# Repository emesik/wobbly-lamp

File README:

wobbly lamp

Lamp which reacts to movement by changing colors.

It associates red, green and blue components with X, Y and Z axes respectively. The deflection from
initial position is linearly converted to light volume in each axis and returns to normal with
decay adjustable by a potentiometer unless the lamp gets bumped again.

Hardware required:
	* 12V supply,
	* MMA7361 accelerometer breakout board,
	* RGB LED strip or other similar light source with common anode,
	* 50x50mm single layer board to make the PCB,
	* electronic components as listed in the KiCad project (ATmega8, 3×N-FET, 3V3 regulator and
	  a bunch of resistors, capacitors and connectors),

This project aims to be an example of ATmega MCU's use of:
	* PWM (pulse width modulation),
	* ADC (analog to digital conversion),
	* interrupts (timer and ADC),

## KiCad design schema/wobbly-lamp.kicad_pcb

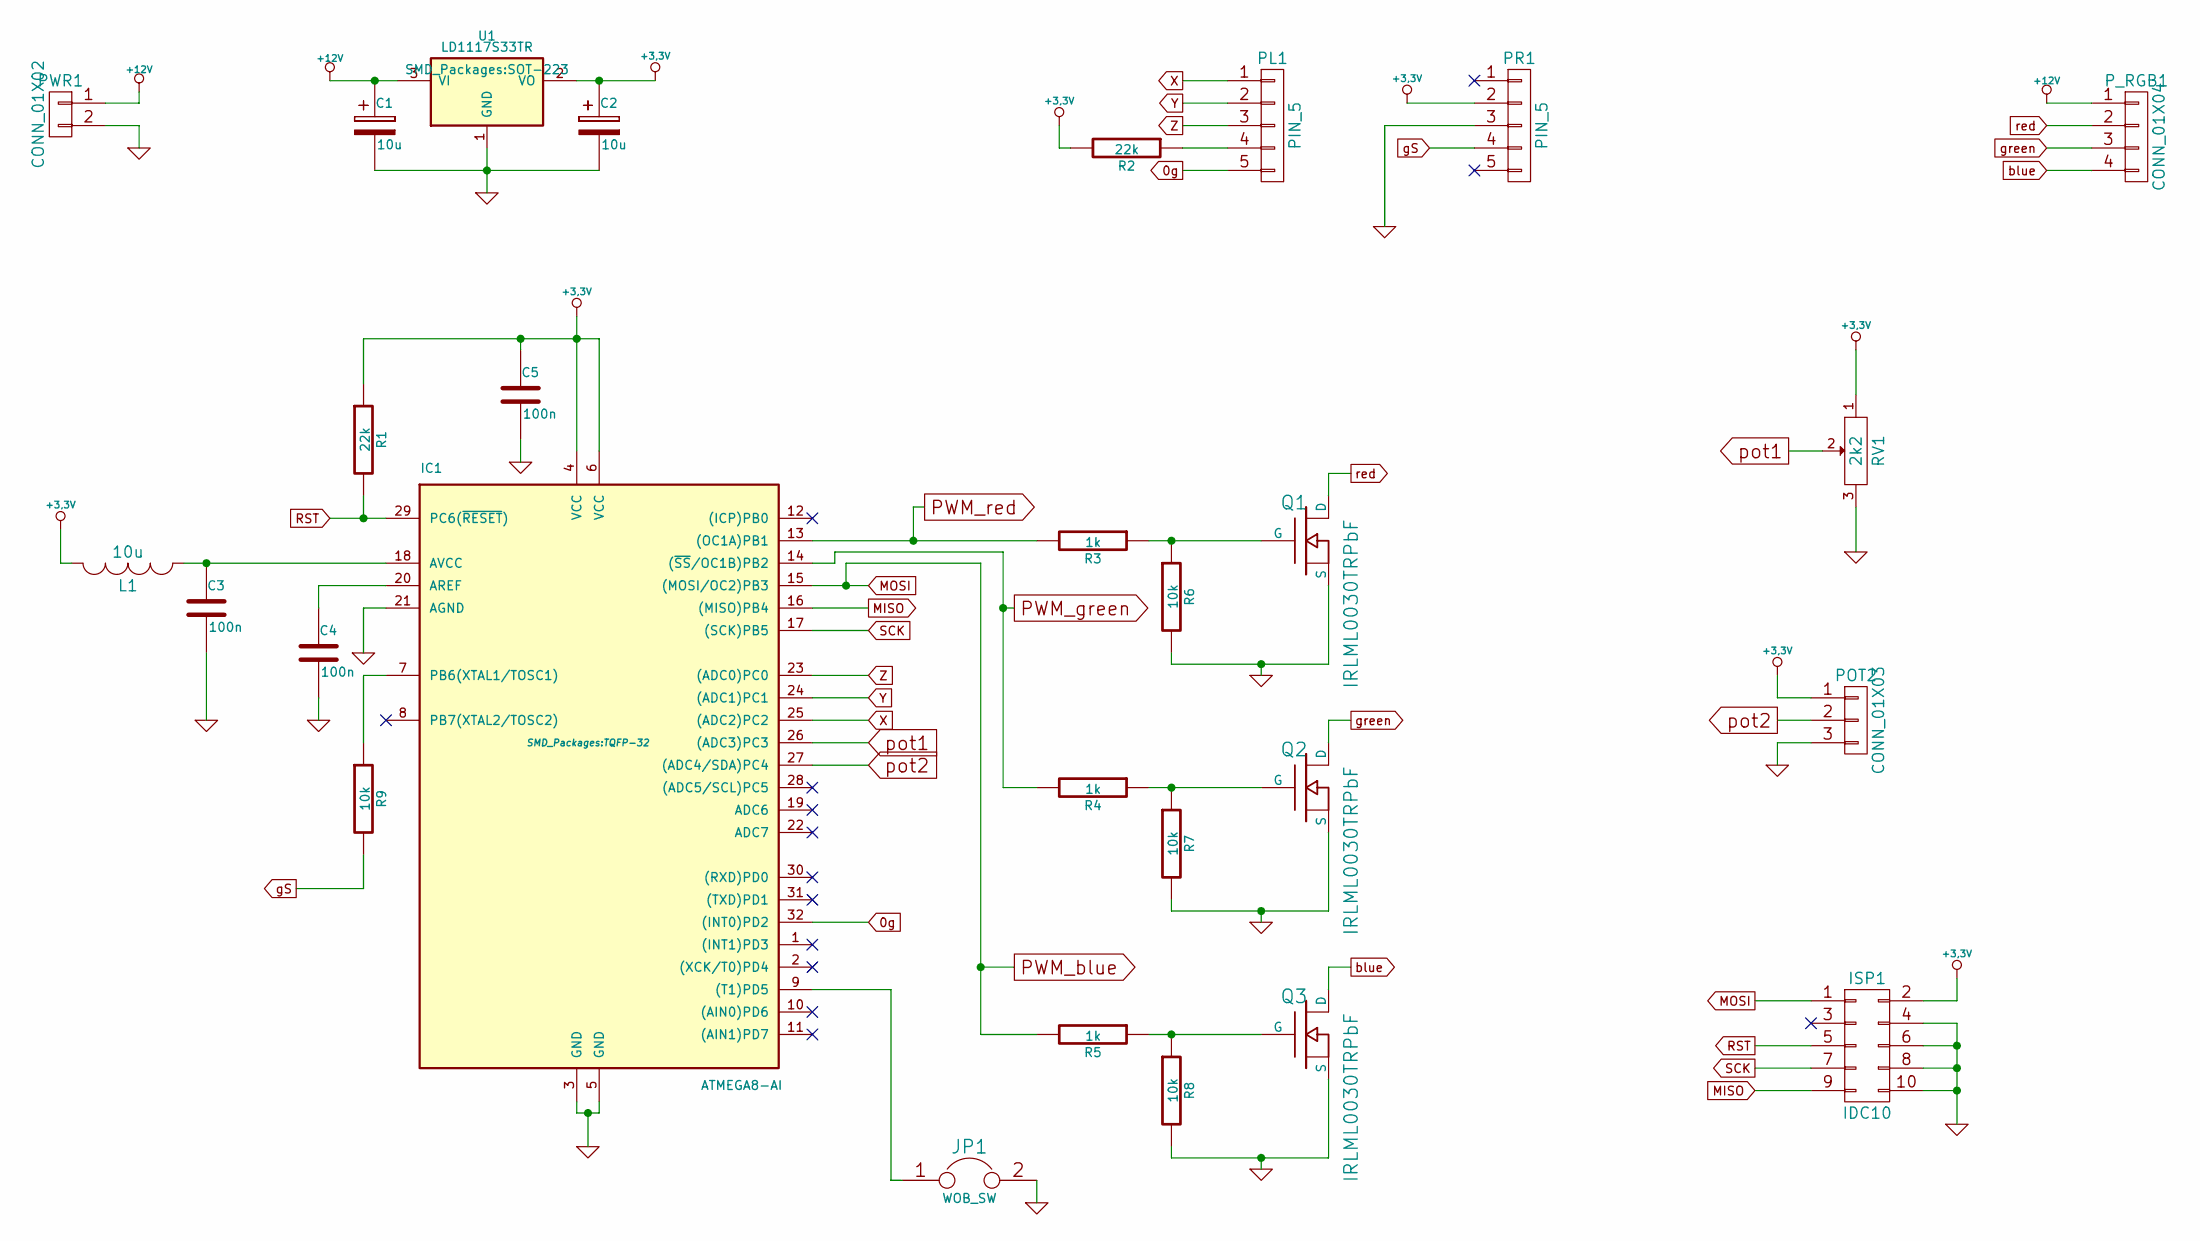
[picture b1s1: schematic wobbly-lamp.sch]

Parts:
C1, C2: 10u; Capacitor5x6RM2.5
C3, C4, C5: 100n; C_0805_HandSoldering
IC1: ATMEGA8-AI; TQFP-32
ISP1: IDC10; Pin_Header_Straight_2x05
JP1: WOB_SW; Pin_Header_Straight_1x02
L1: 10u; SMD-0805
PL1: PIN_5; Pin_Header_Straight_1x05
POT2: CONN_01X03; Pin_Header_Straight_1x03
PR1: PIN_5; Pin_Header_Straight_1x05
PWR1: CONN_01X02; AK300-2
P_RGB1: CONN_01X04; AK300-4
Q1, Q2, Q3: IRLML0030TRPbF; SOT23_FET_Handsoldering
R1, R2: 22k; R_0805_HandSoldering
R3, R4, R5: 1k; R_0805_HandSoldering
R6, R7, R8, R9: 10k; R_0805_HandSoldering
RV1: 2k2; Potentiometer_VishaySpectrol-Econtrim-Type36T
U1: LD1117S33TR; SOT-223

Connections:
0g: IC1.32 ((INT0)PD2), PL1.5
+3.3V: C2.1, C5.1, IC1.4 (VCC), IC1.6 (VCC), ISP1.2, L1.2, POT2.1, PR1.2, R1.1, R2.2, RV1.1, U1.2 (VO)
+12V: C1.1, PWR1.1, P_RGB1.1, U1.3 (VI)
GND: C1.2, C2.2, C3.2, C4.2, C5.2, IC1.3 (GND), IC1.5 (GND), IC1.21 (AGND), ISP1.4, ISP1.6, ISP1.8, ISP1.10, JP1.2, POT2.3, PR1.3, PWR1.2, Q1.S, Q2.S, Q3.S, R6.2, R7.2, R8.2, RV1.3, U1.1 (GND)
MISO: IC1.16 ((MISO)PB4), ISP1.9
unnamed: C3.1, IC1.18 (AVCC), L1.1
unnamed: C4.1, IC1.20 (AREF)
unnamed: IC1.7 (PB6(XTAL1/TOSC1)), R9.1
unnamed: IC1.9 ((T1)PD5), JP1.1
unnamed: PL1.4, R2.1
unnamed: Q1.G, R3.1, R6.1
unnamed: Q2.G, R4.1, R7.1
unnamed: Q3.G, R5.1, R8.1
PWM_blue: IC1.15 ((MOSI/OC2)PB3), ISP1.1, R5.2
PWM_green: IC1.14 ((~SS~/OC1B)PB2), R4.2
PWM_red: IC1.13 ((OC1A)PB1), R3.2
RST: IC1.29 (PC6(~RESET~)), ISP1.5, R1.2
SCK: IC1.17 ((SCK)PB5), ISP1.7
X: IC1.25 ((ADC2)PC2), PL1.1
Y: IC1.24 ((ADC1)PC1), PL1.2
Z: IC1.23 ((ADC0)PC0), PL1.3
blue: P_RGB1.4, Q3.D
gS: PR1.4, R9.2
green: P_RGB1.3, Q2.D
pot1: IC1.26 ((ADC3)PC3), RV1.2
pot2: IC1.27 ((ADC4/SDA)PC4), POT2.2
red: P_RGB1.2, Q1.D

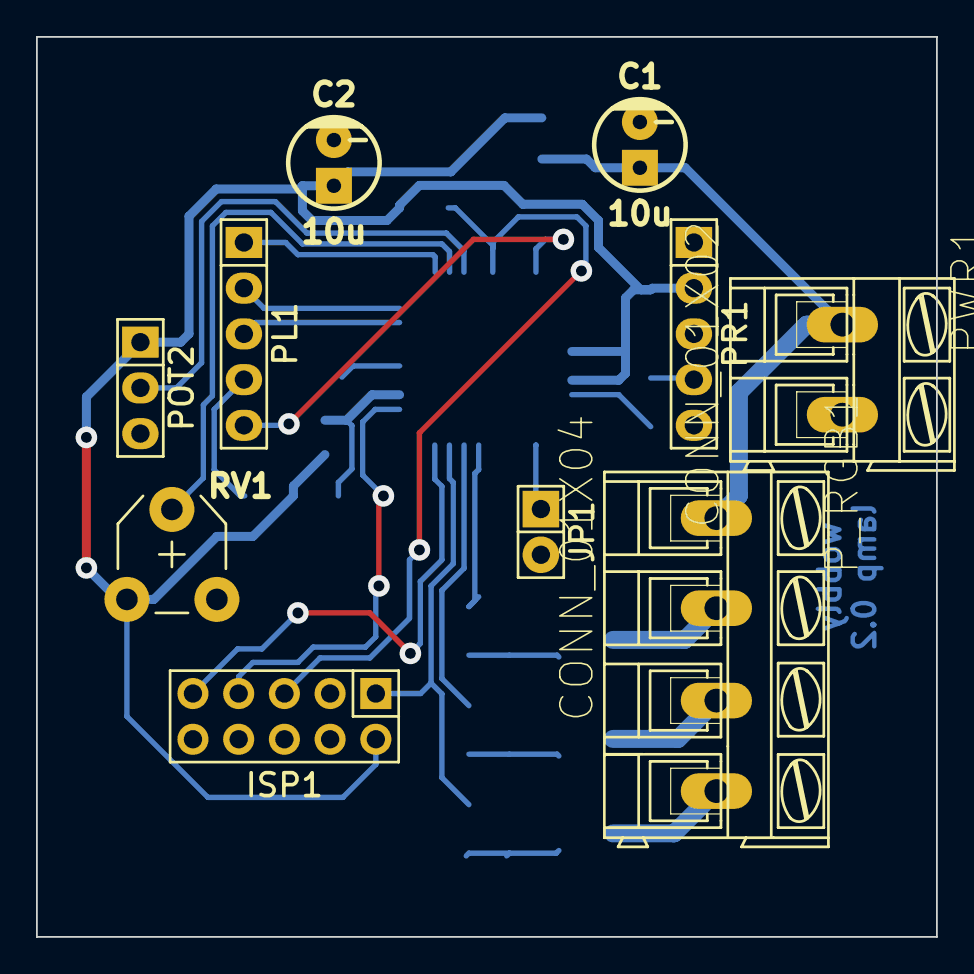
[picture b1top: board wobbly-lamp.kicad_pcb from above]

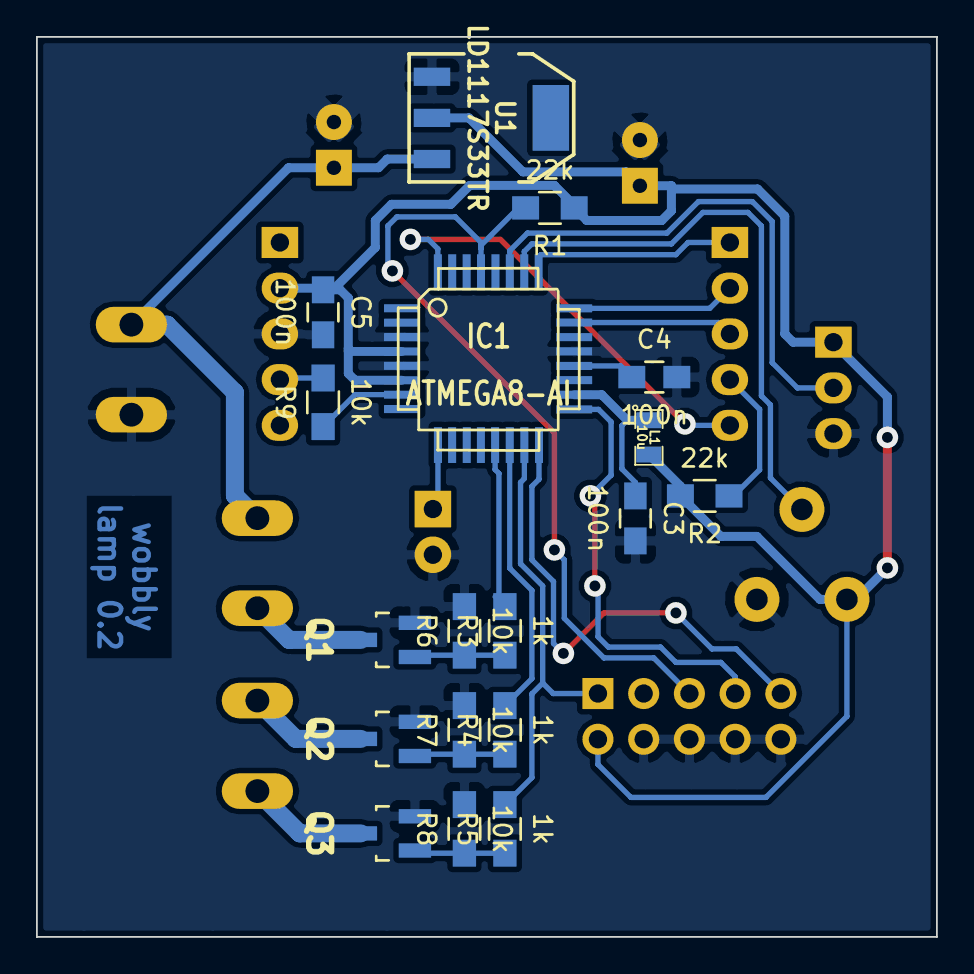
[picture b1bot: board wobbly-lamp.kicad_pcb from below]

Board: 2 copper layers, 50.0 x 50.0 mm, 28 parts (18 on the bottom side), 27 nets.

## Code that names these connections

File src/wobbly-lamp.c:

#include <stdlib.h>
#include <string.h>
#include <avr/interrupt.h>
#include <avr/io.h>
#include <avr/pgmspace.h>
#include <util/delay.h>

// SENSORS is the number of analog inputs we read, while first DOF of them
// are accelerometer's data
#define SENSORS 4
#define DOF 3
#define DECAY_IDX 3
int16_t analog[SENSORS] = {0,0,0,0};	// X, Y, Z, decay
int16_t trail_deflection[DOF] = {0,0,0};	// trailing deflection, subject to decaying
int16_t rest[DOF] = {0,0,-0x28};	// Z adjustment for Earth's g
#define KICK_THRESHOLD 12
#define REST_THRESHOLD 4

// use Vcc as reference, left-adjust result (8b precision)
#define GENERAL_MUX (1 << REFS0) | (1 << ADLAR)
#define ALL_MUX_MASK ((1 << MUX3) | (1 << MUX2) | (1 << MUX1) | (1 << MUX0))
const uint8_t PROGMEM mux_sensors[SENSORS] = {
	(1 << MUX1),	// x @ ADC2
	(1 << MUX0),	// y @ ADC1
	0,				// z @ ADC0
	(1 << MUX1) | (1 << MUX0),	// decay @ ADC3
};
#define LOWER_SENS_THR 0xa0
#define RAISE_SENS_THR 0x20
uint8_t inlowsensmode = 0;	// 6g instead of 1.5g enabled

#define BASE_LIGHT_VOLUME	0xa0
int16_t level[DOF] = {BASE_LIGHT_VOLUME, BASE_LIGHT_VOLUME, BASE_LIGHT_VOLUME};
uint16_t decay_period = 0x10;

const uint8_t PROGMEM gamma[0x100] = {
	0,  0,  0,  0,  0,  0,  0,  0,  0,  0,  0,  0,  0,  0,  0,  0,
	0,  0,  0,  0,  0,  0,  0,  0,  0,  0,  0,  0,  1,  1,  1,  1,
	1,  1,  1,  1,  1,  1,  1,  1,  1,  2,  2,  2,  2,  2,  2,  2,
	2,  3,  3,  3,  3,  3,  3,  3,  4,  4,  4,  4,  4,  5,  5,  5,
	5,  6,  6,  6,  6,  7,  7,  7,  7,  8,  8,  8,  9,  9,  9, 10,
	10, 10, 11, 11, 11, 12, 12, 13, 13, 13, 14, 14, 15, 15, 16, 16,
	17, 17, 18, 18, 19, 19, 20, 20, 21, 21, 22, 22, 23, 24, 24, 25,
	25, 26, 27, 27, 28, 29, 29, 30, 31, 32, 32, 33, 34, 35, 35, 36,
	37, 38, 39, 39, 40, 41, 42, 43, 44, 45, 46, 47, 48, 49, 50, 50,
	51, 52, 54, 55, 56, 57, 58, 59, 60, 61, 62, 63, 64, 66, 67, 68,
	69, 70, 72, 73, 74, 75, 77, 78, 79, 81, 82, 83, 85, 86, 87, 89,
	90, 92, 93, 95, 96, 98, 99,101,102,104,105,107,109,110,112,114,
	115,117,119,120,122,124,126,127,129,131,133,135,137,138,140,142,
	144,146,148,150,152,154,156,158,160,162,164,167,169,171,173,175,
	177,180,182,184,186,189,191,193,196,198,200,203,205,208,210,213,
	215,218,220,223,225,228,231,233,236,239,241,244,247,249,252,255};

// the default white balance
const int16_t PROGMEM bias[DOF] = {10,6,-6};

#define	RED		OCR1A
#define	GREEN	OCR1B
#define	BLUE	OCR2

void init_lights() {
	DDRB |= (1 << PB1) | (1 << PB2) | (1 << PB3);
	PORTB |= (1 << PB1) | (1 << PB2) | (1 << PB3);
	// timers on /8 prescalers, phase-correct PWM
	TCCR1A = (1 << COM1A1) | (1 << COM1B1) | (1 << WGM10);
	TCCR1B = (1 << CS11);
	TCCR2 = (1 << WGM20) | (1 << COM21) | (1 << CS21);
	RED = GREEN = BLUE = 0;
}

inline void go_lowsens() {
	PORTB |= (1 << PB6);
	inlowsensmode = 1;
}

inline void go_hisens() {
	PORTB &= ~(1 << PB6);
	inlowsensmode = 0;
}

void init_sensors() {
	// X, Y, Z, decay inputs
	DDRC = 0xff & ~((1 << PC3) | (1 << PC2) | (1 << PC1) | (1 << PC0));
	DDRD &= ~(1 << PD2);									// 0g digital
	DDRB |= (1 << PB6);										// g-select digital output
	go_lowsens();
	ADMUX = GENERAL_MUX | pgm_read_byte(&mux_sensors[0]);
	// enable ADC, turn on interrupt, /128 prescaler giving 62,5kHz
	ADCSRA = (1 << ADEN) | (1 << ADIE) | (1 << ADPS2) | (1 << ADPS1) | (1 << ADPS0);
	// start first conversion
	ADCSRA |= (1 << ADSC);
}

ISR(ADC_vect) {
	static uint8_t inc_sens = 1, dec_sens = 0;
	int16_t val;
	uint8_t sensor = 0;	// currently measured axis

	// check which axis has been measured
	for (sensor = 0; sensor < DOF; sensor++) {
		if ((ADMUX & ALL_MUX_MASK) == pgm_read_byte(&mux_sensors[sensor]))
			break;
	}

	// read the analog value
	val = ADCH;
	if (sensor < DOF) {
		// X, Y, Z get normalized to 0
		val -= 0x80;
		// rescale 6g to 1.5g if we are in low sensitivity mode
		if (inlowsensmode) val = val * 4;
	}

	// store the value
	analog[sensor] = val;
	// next input
	sensor = (sensor + 1) % SENSORS;

	// If ANY axis had high value, we should probably go to lower sensitivity mode.
	// If ALL axes have low values, we might enable hi sensitivity mode.
	if (sensor < DOF) {
		if (abs(val) > LOWER_SENS_THR) dec_sens = 1;
		if (abs(val) >= RAISE_SENS_THR) inc_sens = 0;
	}

	if (sensor == 0) {	// once all sensors have been probed
		// set sensitivity
		if (!inlowsensmode && dec_sens) {
			// TODO: never happens. why?
			go_lowsens();
		}
		if (inlowsensmode && inc_sens && !dec_sens) {
			go_hisens();
		}

		// reset all local flags
		inc_sens = 1;
		dec_sens = 0;

		for (uint8_t i=0; i < DOF; i++) {
			int16_t defl;
			// if current deflection from rest is bigger than the decaying one,
			// use it as the new value
			defl = analog[i] - rest[i];
			if (abs(defl) < REST_THRESHOLD) defl = 0;
			if (abs(defl) > abs(trail_deflection[i]) + KICK_THRESHOLD)
				trail_deflection[i] = defl;
		}
	}

	// reset all MUX bits then set to next axis
	ADMUX = GENERAL_MUX | pgm_read_byte(&mux_sensors[sensor]);

	// start conversion again
	ADCSRA |= (1 << ADSC);
}

void init_decay() {
	TCCR0 |= (1 << CS01) | (1 << CS00);	// prescaler /64
	TIMSK |= (1 << TOIE0);
}

uint8_t get_pwm_value(uint8_t color, int16_t lev) {
	lev += pgm_read_word(&bias[color]);
	// make sure that level is within bounds
	if (lev < 0) lev = 0;
	if (lev > 0xff) lev = 0xff;
	return pgm_read_byte(&gamma[(uint8_t)lev]);
}

ISR(TIMER0_OVF_vect) {
	static uint16_t decay_overflows = 0;
	uint8_t ax;
	int16_t d;

	// disable interrupts
	cli();

	// do the decay
	if (++decay_overflows >= analog[DECAY_IDX]) {
		for (ax=0; ax<DOF; ax++) {
			if (trail_deflection[ax] > 0) trail_deflection[ax]--;
			else if (trail_deflection[ax] < 0) trail_deflection[ax]++;
		}
		decay_overflows = 0;
	}

	// deflections to levels
	d = 0;
	for (ax=0; ax<DOF; ax++) {
		level[ax] = trail_deflection[ax] + BASE_LIGHT_VOLUME;
		d += trail_deflection[ax];
	}
	d = d / DOF;
	// equalize total light amount
	// what is added to one channel gets subtracted from others
	for (ax=0; ax<DOF; ax++) {
		level[ax] -= d;
	}
	RED   = get_pwm_value(0, level[0]);
	GREEN = get_pwm_value(1, level[1]);
	BLUE  = get_pwm_value(2, level[2]);

	sei();
}

int main()
{
	init_lights();
	sei();
	init_sensors();
	// make sure we have some stable measurement
	_delay_ms(100);
	// store current position as rest
	// TODO: update rest on inactivity
	for (int ax=0; ax<DOF; ax++) {
		rest[ax] = analog[ax];
	}
	// now we can initialize the decay timer
	init_decay();
	while (1) {};
}

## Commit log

2014-11-28 Add schema
2014-11-28 Add initial code
2014-11-28 Redraw PCB
2014-11-28 Add .gitignore
2014-11-30 Add missing path
2014-12-02 Remove all stuff related to LCD, the working PCB doesn't support it
2014-12-02 Add first working PCB, tiny version
2014-12-08 Determine current axis by re-reading of ADMUX instead of global counter
2014-12-08 Add initial rest, decay calculation and white balance bias
2014-12-08 Reorder, clean up
2014-12-08 Read decay period from potentiometer, use phase correct PWM
2014-12-08 Add some README
2014-12-08 Fix bug with potentiometer input treated as signed value
2014-12-08 Clean up and update comments
2014-12-08 Fix reverse equalization of light volume
2014-12-08 Define base light volume and set it to higher value
